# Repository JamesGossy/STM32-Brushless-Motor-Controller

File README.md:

<div align="center">

# STM32 Brushless Motor Controller

A custom four-layer motor controller with bare-metal field-oriented control on an STM32G474. The project includes the PCB design, C firmware, a motor simulator and a live control dashboard.

*Real motor bench test with the live telemetry dashboard.*

</div>

## Engineering overview

- **Hardware:** a 57 × 75 mm PCB with six MOSFETs, three low-side current shunts, absolute encoder feedback and CAN connectivity.
- **Control:** 20 kHz d/q current loops and SVPWM, a 2 kHz speed loop, decoupling feedforward and field weakening.
- **Firmware:** bare-metal C using CMSIS headers, with register-level peripheral drivers and no STM32 HAL dependency. The application code also runs in the software-in-the-loop simulator.
- **Calibration and protection:** current-sense polarity and encoder calibration, stored settings, and checks for current, voltage, temperature, encoder and communication faults.
- **Tools:** a browser dashboard for commands and telemetry, plus unit tests and simulated motor/fault scenarios.

```mermaid
flowchart LR
    control["STM32G474<br/>Field-oriented control"]
    power["DRV8353S & MOSFETs<br/>Three-phase bridge"]
    motor["BLDC / PMSM motor"]
    control -->|PWM| power --> motor
    motor -->|Current & rotor position| control

    classDef controller fill:#eef2ff,stroke:#6366f1,color:#1e1b4b
    classDef drive fill:#ecfdf5,stroke:#059669,color:#064e3b
    class control controller
    class power,motor drive
```

## Hardware

| Item | Design |
| --- | --- |
| MCU | STM32G474RET6, 170 MHz |
| Gate driver | TI DRV8353S, configured over SPI |
| Input range | 12–60 V design target |
| Phase current | 25 A continuous design target; firmware defaults to a 20 A limit |
| MOSFETs | Six IAUCN08S7N019ATMA1, 80 V |
| Current sensing | Three 2 mΩ shunts with Kelvin connections |
| Position feedback | MA730 SPI encoder; external quadrature interface |
| PWM | HRTIM, 20 kHz, 200 ns dead time |
| Interfaces | CAN, USB CDC, UART and SWD |
| PCB | 57 × 75 mm, four layers |

The layout keeps gate-drive loops short, separates current-sense connections from power routing, and uses copper pours and via arrays to distribute current and heat. KiCad sources and manufacturing files are in [`controller_hardware/`](controller_hardware/).

## Live dashboard

The dashboard connects to either the simulator or a board over USB. It shows motor telemetry and accepts commands for speed, torque, calibration and fault handling. The GIF above shows the simulator.

## Try the simulator

On Windows, run `controller_firmware\tools\setup.bat` to install missing tools, build the simulator and run tests. Then run `controller_firmware\tools\dashboard.bat` to open the dashboard.

For a manual build, install CMake, Ninja, a host C compiler and Python:

```sh
cd controller_firmware
cmake --preset sim
cmake --build --preset sim
ctest --preset sim
python -m pip install -r tools/dashboard/requirements.txt
python tools/dashboard/plot_motor.py --sim
```

Open [localhost:8988](http://localhost:8988). In the dashboard console, run `calibrate`, then `motor 3000` to request 3,000 rpm. Use `motor off` to stop. Simulator commands such as `sim load 0.1` and `sim lock on` exercise load response and fault handling.

## Build for the board

Install STM32CubeCLT and put its Arm compiler, CMake, Ninja and STM32 programmer on PATH. From `controller_firmware/`:

```sh
cmake --preset default
cmake --build --preset default
cmake --build build --target flash
```

Flashing uses ST-Link over SWD. To connect the dashboard to the board:

```sh
python tools/dashboard/plot_motor.py --serial COM5
```

Set the motor parameters and limits in [`app/config.h`](controller_firmware/app/config.h) before running hardware. Start with a current-limited supply and an unloaded motor, then run calibration before requesting motion.

## Validation and limits

C tests cover control maths, SVPWM, configuration, commands and telemetry. Software-in-the-loop tests exercise calibration, torque and speed response, field weakening, CAN control and fault handling. CI builds the firmware and runs simulator and dashboard tests on Linux and Windows.

The electrical ratings above are design targets; simulation does not establish continuous-current capability or thermal performance. This board revision has no on-board reverse-polarity protection, fuse or bus TVS.

## Code guide

| Location | Contents |
| --- | --- |
| [`controller_hardware/`](controller_hardware/) | KiCad schematics, PCB layout and manufacturing files |
| [`controller_firmware/app/`](controller_firmware/app/) | FOC, control loops, calibration, commands and telemetry |
| [`controller_firmware/hal/stm32g474/`](controller_firmware/hal/stm32g474/) | HRTIM, ADC, encoder, gate-driver, CAN and USB drivers |
| [`controller_firmware/sim/`](controller_firmware/sim/) | Simulated hardware interface, motor model and TCP server |
| [`controller_firmware/tests/`](controller_firmware/tests/) | Unit and motor simulation tests |
| [`controller_firmware/tools/dashboard/`](controller_firmware/tools/dashboard/) | Browser dashboard and Python bridge |

MIT licensed. Copyright © 2026 James Goss.

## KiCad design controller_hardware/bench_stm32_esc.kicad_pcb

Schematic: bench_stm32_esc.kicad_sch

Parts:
C1, C2, C3, C4, C7: EEHZC1K470V; CAP-SMD_BD10.0-L10.3-W10.3-FD; MPN EEHZC1K470V; LCSC Part C454280
C5, C12, C30, C31, C33, C41, C46, C47, C48, C49, C50, C53, C64, C65, C76, C83: 100nF; C_0402; Voltage Rated 16V; Tolerance ±10%; Part CL05B104KO5NNNC; LCSC C1525
C6, C38: 47nF; C_0603; Voltage Rated 100V; Tolerance ±10%; Part 0603B473K101CT; LCSC C559308
C8, C11, C20, C22: 100nF; C_0402; Voltage Rated 100V; Tolerance ±10%; Part GRM155R62A104KE14D; LCSC C162178
C9: GRM32EC72A106KE05L; C1210; MPN GRM32EC72A106KE05L; LCSC Part C576517
C10, C17, C19: 47uF; C_1206; Voltage Rated 16V; Tolerance ±20%; Part 1206X476M160NT; LCSC C172351
C13, C14, C15, C29, C36, C37, C42, C43, C45, C52, C93: 1uF; C_0402; Voltage Rated 25V; Tolerance ±10%; Part CL05A105KA5NQNC; LCSC C52923
C18, C26, C32: 2.2nF; C_0402; Voltage Rated 100V; Tolerance ±10%; Part CC0402KRX7R0BB222; LCSC C576731
C21, C24, C25: 1nF; C_0402; Voltage Rated 100V; Tolerance ±10%; Part CC0402KRX7R0BB102; LCSC C527013
C23, C27, C28: 1uF; C_1206; Voltage Rated 100V; Tolerance ±10%; Part CL31B105KCHNNNE; LCSC C13832
C39, C40: 2.2nF; C_0402; Voltage Rated 50V; Tolerance ±10%; Part 0402B222K500NT; LCSC C1531
C44: 4.7uF; C_0402; Voltage Rated 10V; Tolerance ±20%; Part CL05A475MP5NRNC; LCSC C23733
C51, C66, C67: 1nF; C_0402; Voltage Rated 50V; Tolerance ±10%; Part 0402B102K500NT; LCSC C1523
C54, C55: 2.2uF; C_0402; Voltage Rated 25V; Tolerance ±20%; Part GRM155R61E225ME15D; LCSC C72203
C56, C57, C58: 10nF; C_0402; Voltage Rated 50V; Tolerance ±10%; Part CL05B103KB5NNNC; LCSC C15195
C61, C62, C63: 47nF; C_0402; Voltage Rated 50V; Tolerance ±10%; Part 0402B473K500NT; LCSC C82219
C68, C69, C70, C71, C72, C73: 4.7uF; C_1206; Voltage Rated 100V; Tolerance ±10%; Part GRM31CC72A475KE11L; LCSC C237304
C85, C87: 18pF; C_0402; Voltage Rated 50V; Tolerance ±5%; Part 0402CG180J500NT; LCSC C1549
CN1, CN2, CN3: 1053141104; CONN-TH_4P-P2.50_MOLEX_1053141104; MPN 1053141104; LCSC Part C841207
D1: White; D_0603; Part KT-0603W; LCSC C2290
D2: Green; D_0805; Part KT-0805G; LCSC C2297
D3: PESD2CAN,215; SOT-23-3_L2.9-W1.3-P1.90-LS2.4-BR; MPN PESD2CAN,215; LCSC Part C75176
D4: Red; D_0805; Forward Voltage (VF) 1.6V~2.6V; Part NCD0805R1; LCSC C84256
D6: Yellow; D_0805; Part KT-0805Y; LCSC C2296
FB1: FB_0603; Current Rating 200mA; Tolerance ±25%; Part GZ1608D601TF; LCSC C1002
FB2: FB_0603; Current Rating 2A; Tolerance ±25%; Part BLM18PG121SN1D; LCSC C14709
H1, H2, H3, H4: MountingHole; MountingHole_3.2mm_M3
J1: Conn_02x01; PinHeader_2x01_P2.54mm_Vertical
J2: USB_C_Receptacle_USB2.0_16P; USB_C_Receptacle_HRO_TYPE-C-31-M-12
J3: Conn_ARM_SWD_TagConnect_TC2030-NL; Tag-Connect_TC2030-IDC-NL_2x03_P1.27mm_Vertical
J4: Screw_Terminal_01x05; CUI_TB005_-762-05BE
L1: FNR4020S8R2MT; IND-SMD_L4.0-W4.0_FNR40XXS; MPN FNR4020S8R2MT; LCSC Part C167834
NT1, NT2, NT3, NT4, NT5, NT6: NetTie_2; NetTie-2_SMD_Pad0.5mm
NT7: NetTie_2; NetTie-2_SMD_Pad2.0mm
Q1, Q2, Q3, Q4, Q5, Q6: IAUCN08S7N019ATMA1; TDSON-8-1; LCSC C33993693
R1, R2, R42, R44, R45, R46, R47, R48, R49, R56: 100Ω; R_0402; Overload Voltage (Max) 50V; Tolerance ±1%; Part 0402WGF1000TCE; LCSC C25076
R3, R4, R5: 330Ω; R_0402; Overload Voltage (Max) 50V; Tolerance ±1%; Part 0402WGF3300TCE; LCSC C25104
R6, R23, R51: 100kΩ; R_0402; Overload Voltage (Max) 50V; Tolerance ±1%; Part 0402WGF1003TCE; LCSC C25741
R7, R10, R13: 2.7Ω; R_0805; Overload Voltage (Max) 150V; Tolerance ±1%; Part 0805W8F270KT5E; LCSC C17532
R8, R9, R12: 2mΩ; R_2512_6332Metric; Part No HoLLR2512-3W-2mR-1%; LCSC C2994640
R11: 19.1kΩ; R_0402; Overload Voltage (Max) 50V; Part 0402WGF1912TCE; LCSC C52036
R14: 120Ω; R_0402; Overload Voltage (Max) 50V; Tolerance ±1%; Part 0402WGF1200TCE; LCSC C25079
R15, R16, R20: 56Ω; R_0402; Overload Voltage (Max) 50V; Tolerance ±1%; Part 0402WGF560JTCE; LCSC C25127
R17, R21: 4.7kΩ; R_0402; Overload Voltage (Max) 50V; Tolerance ±1%; Part 0402WGF4701TCE; LCSC C25900
R18: 383kΩ; R_0805; Overload Voltage (Max) 150V; Tolerance ±1%; Part 0805W8F3833T5E; LCSC C17652
R19: 9.76kΩ; R_0805; Overload Voltage (Max) 150V; Tolerance ±1%; Part 0805W8F9761T5E; LCSC C17859
R22, R24, R43, R50, R53: 10kΩ; R_0402; Overload Voltage (Max) 50V; Tolerance ±1%; Part 0402WGF1002TCE; LCSC C25744
R25, R26, R27, R28, R31, R32: 10Ω; R_0402; Overload Voltage (Max) 50V; Tolerance ±1%; Part 0402WGF100JTCE; LCSC C25077
R29, R30: 5.1kΩ; R_0402; Overload Voltage (Max) 50V; Tolerance ±1%; Part 0402WGF5101TCE; LCSC C25905
R33, R35, R37: 383kΩ; R_0402; Overload Voltage (Max) 75V; Tolerance ±1%; Part RK73H1ETTP3833F; LCSC C317011
R34, R36, R41, R55: 1kΩ; R_0402; Overload Voltage (Max) 50V; Tolerance ±1%; Part 0402WGF1001TCE; LCSC C11702
R38, R39, R40: 9.76kΩ; R_0402; Overload Voltage (Max) 50V; Tolerance ±1%; Part FRC0402F9761TS; LCSC C2998101
R52, R54: 20kΩ; R_0402; Overload Voltage (Max) 50V; Tolerance ±1%; Part 0402WGF2002TCE; LCSC C25765
S1, S2: Tactile Button, 160gf; SW_TS-1088-AR02016; Voltage Rating (Dc) 12V; Part TS-1088-AR02016; LCSC C720477
TH1, TH2: Thermistor_NTC; R_0603; Part No KNTC0603/10KF3950; LCSC C2892547
TP1, TP6, TP7, TP8, TP9, TP10, TP11, TP12, TP13: TestPoint; TestPoint_Pad_1.5x1.5mm
U1: LMR51635YDDCR; SOT-23-6_L2.9-W1.6-P0.95-LS2.8-BL; MPN LMR51635YDDCR; LCSC Part C45262770
U2: MA730; QFN-16-1EP_3x3mm_P0.5mm_EP1.75x1.75mm
U3: TPD1E05U06DYA; D_SOD-523
U4: DRV8353SRTAR; WQFN-40_L6.0-W6.0-P0.50-TL-EP4.5; MPN DRV8353SRTAR; LCSC Part C701785
U5: LM66200DRLR; SOT-583-8_L2.1-W1.2-P0.50-LS1.6-BL; MPN LM66200DRLR; LCSC Part C3235556
U6: AP2112K-3.3; SOT-23-5
U7: STM32G474RETx; LQFP-64_10x10mm_P0.5mm
U8: TCAN1462VDRBRQ1; DFN-8_L3.0-W3.0-P0.65-TL-EP2.4; MPN TCAN1462VDRBRQ1; LCSC Part C5215833
U20: USBLC6-2P6; SOT-666
X1: X322524MOB4SI; CRYSTAL-SMD_4P-L3.2-W2.5-BL; MPN X322524MOB4SI; LCSC Part C70590

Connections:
5V_OR: C31.2, C36.1, C43.1, CN3.2, TP12.1 (1_1), U5.2 (VOUT), U5.7 (VOUT), U6.1 (VIN), U6.3 (EN), U8.3 (VCC)
+3V3: C11.1, C29.1, C30.1, C33.2, C44.1, C45.1, C46.1, C47.1, C48.1, C49.1, C53.1, C93.1, D4.2, D6.2, FB1.2, J3.1 (VCC), R17.1, R21.1, R22.1, R23.1, R43.1, R55.1, S2.1 (A), TP13.1 (1_1), U2.13 (VDD), U4.24 (VREF), U6.5 (VOUT), U7.1 (VBAT), U7.16 (VDD), U7.32 (VDD), U7.48 (VDD), U7.64 (VDD), U8.5 (NC/VIO)
+3V3A: C50.1, C52.1, C83.1, FB1.1, U7.28 (VREF+), U7.29 (VDDA)
+5V_BUCK: C10.1, C17.1, C19.1, C37.1, L1.2, R6.1, U5.6 (VIN2)
+5V_USB: C42.1, C55.1, FB2.2, U5.3 (VIN1)
/AMB_TMP: C12.1, R21.2, R48.1, TH2.1
/AMB_TMP_ADC: C64.1, R48.2, U7.10 (PC2)
/BOOT0: R24.1, S2.2 (B), U7.61 (PB8)
/CANH: CN1.4, CN2.4, D3.1, J1.2, U8.7 (CANH)
/CANL: CN1.3, CN2.3, D3.2, R14.1, U8.6 (CANL)
/CAN_RX: U7.58 (PB5), U8.4 (RXD)
/CAN_TX: U7.59 (PB6), U8.1 (TXD)
/CB: C22.2, U1.6 (CB)
/CC1: J2.A5 (CC1), R30.1
/CC2: J2.B5 (CC2), R29.1
/CPH: C6.2, U4.2 (CPH)
/CPL: C6.1, U4.1 (CPL)
/D+: J2.A6 (D+), J2.B6 (D+), U20.1 (I/O2)
/D-: J2.A7 (D-), J2.B7 (D-), U20.6 (I/O1)
/DVDD: C15.1, U4.38 (DVDD)
/ENABLE: D2.2, U4.31 (ENABLE), U7.57 (PB4)
/ENC_CS: U2.5 (~CS), U7.33 (PB11)
/FAULT: R4.2, R22.2, U4.26 (nFAULT)
/FB: R6.2, R11.1, U1.1 (FB)
/GD_CS: R43.2, U4.30 (nSCS), U7.52 (PC10)
/GHA: R27.1, U4.6 (GHA)
/GHA_R: Q1.4 (G), R27.2
/GHB: R26.1, U4.15 (GHB)
/GHB_R: Q3.4 (G), R26.2
/GHC: R25.1, U4.16 (GHC)
/GHC_R: Q5.4 (G), R25.2
/GLA: R32.1, U4.8 (GLA)
/GLA_R: Q2.4 (G), R32.2
/GLB: R31.1, U4.13 (GLB)
/GLB_R: Q4.4 (G), R31.2
/GLC: R28.1, U4.18 (GLC)
/GLC_R: Q6.4 (G), R28.2
/HEARBEAT: D1.2, U7.18 (PA4)
/HSE_IN: C87.1, U7.5 (PF0), X1.3 (OSC2)
/HSE_OUT: C85.1, U7.6 (PF1), X1.1 (OSC1)
/IA: C56.1, R20.1, U7.37 (PB15)
/IB: C57.1, R16.1, U7.36 (PB14)
/IC: C58.1, R15.1, U7.35 (PB13)
/INHA: U4.32 (INHA), U7.43 (PA9)
/INHB: U4.34 (INHB), U7.41 (PC9)
/INHC: U4.36 (INHC), U7.39 (PC7)
/INLA: U4.33 (INLA), U7.42 (PA8)
/INLB: U4.35 (INLB), U7.40 (PC8)
/INLC: U4.37 (INLC), U7.38 (PC6)
/MOTA: C18.1, J4.2, NT1.2, Q1.1 (S), Q1.2 (S), Q1.3 (S), Q2.5 (D), R33.1, TP8.1 (1_1)
/MOTB: C26.1, J4.3, NT3.2, Q3.1 (S), Q3.2 (S), Q3.3 (S), Q4.5 (D), R35.1, TP6.1 (1_1)
/MOTC: C32.1, J4.5, NT5.2, Q5.1 (S), Q5.2 (S), Q5.3 (S), Q6.5 (D), R37.1, TP7.1 (1_1)
/NRST: C76.1, J3.3 (~RESET), S1.2 (B), U7.7 (PG10)
/ON: R51.1, U5.4 (~ON)
/PHASE_TMP: C5.1, R17.2, R49.1, TH1.1
/PHASE_TMP_ADC: C65.1, R49.2, U7.11 (PC3)
/QUAD_CH1: C40.1, R50.2, R52.1, U7.12 (PA0)
/QUAD_CH1_CONN: CN3.4, R50.1
/QUAD_CH2: C39.1, R53.2, R54.1, U7.13 (PA1)
/QUAD_CH2_CONN: CN3.3, R53.1
/SHA: NT1.1, U4.7 (SHA)
/SHB: NT3.1, U4.14 (SHB)
/SHC: NT5.1, U4.17 (SHC)
/SNA: NT2.1, R2.2
/SNA_FILT: C21.2, R2.1, U4.10 (SNA)
/SNB: NT4.1, R44.2
/SNB_FILT: C24.2, R44.1, U4.11 (SNB)
/SNC: NT6.1, R46.2
/SNC_FILT: C25.2, R46.1, U4.20 (SNC)
/SOA: R20.2, U4.23 (SOA)
/SOB: R16.2, U4.22 (SOB)
/SOC: R15.2, U4.21 (SOC)
/SPA: Q2.1 (S), Q2.2 (S), Q2.3 (S), R1.2, R8.1
/SPA_FILT: C21.1, R1.1, U4.9 (SPA)
/SPB: Q4.1 (S), Q4.2 (S), Q4.3 (S), R9.1, R42.2
/SPB_FILT: C24.1, R42.1, U4.12 (SPB)
/SPC: Q6.1 (S), Q6.2 (S), Q6.3 (S), R12.1, R45.2
/SPC_FILT: C25.1, R45.1, U4.19 (SPC)
/SPI_MISO: R55.2, U2.7 (MISO), U4.27 (SDO), U7.20 (PA6)
/SPI_MOSI: U2.4 (MOSI), U4.28 (SDI), U7.21 (PA7)
/SPI_SCK: U2.12 (SCLK), U4.29 (SCLK), U7.19 (PA5)
/ST: R23.2, U5.8 (ST)
/SW: C22.1, L1.1, U1.5 (SW)
/SWCLK: J3.4 (SWCLK), U7.50 (PA14)
/SWDIO: J3.2 (SWDIO), U7.49 (PA13)
/SWO: J3.6 (SWO), U7.56 (PB3)
/USB_D+: U7.46 (PA12), U20.3 (I/O2)
/USB_D-: U7.45 (PA11), U20.4 (I/O1)
/USB_VBUS: C54.1, FB2.1, J2.A4 (VBUS), J2.A9 (VBUS), J2.B4 (VBUS), J2.B9 (VBUS), U20.5 (VBUS)
/VA_ADC: C51.1, R41.1, U7.26 (PB2)
/VB_ADC: C66.1, R36.1, U7.25 (PB1)
/VCP: C14.1, U4.5 (VCP)
/VC_ADC: C67.1, R34.1, U7.24 (PB0)
/VDC_ADC: C41.1, R47.2, U7.9 (PC1)
/VDRAIN: C14.2, NT7.1, U4.4 (VDRAIN)
/VGLS: C13.1, U4.40 (VGLS)
/VSENA: C61.1, R33.2, R40.1, R41.2
/VSENB: C62.1, R35.2, R36.2, R39.1
/VSENC: C63.1, R34.2, R37.2, R38.1
/VSENVM: C38.1, R18.2, R19.1, R47.1, U3.1 (I/O)
GND: C1.2, C2.2, C3.2, C4.2, C5.2, C7.2, C8.2, C9.1, C10.2, C11.2, C12.2, C13.2, C15.2, C17.2, C19.2, C20.2, C23.1, C27.1, C28.1, C29.2, C30.2, C31.1, C33.1, C36.2, C37.2, C38.2, C39.2, C40.2, C41.2, C42.2, C43.2, C44.2, C45.2, C46.2, C47.2, C48.2, C49.2, C50.2, C51.2, C52.2, C53.2, C54.2, C55.2, C56.2, C57.2, C58.2, C61.2, C62.2, C63.2, C64.2, C65.2, C66.2, C67.2, C68.2, C69.2, C70.2, C71.2, C72.2, C73.2, C76.2, C83.2, C85.2, C87.2, C93.2, CN1.1, CN1.2, CN2.1, CN2.2, CN3.1, D3.3, J2.A1 (GND), J2.A12 (GND), J2.B1 (GND), J2.B12 (GND), J2.SH (SHIELD), J3.5 (GND), J4.4, NT2.2, NT4.2, NT6.2, R3.2, R5.2, R7.2, R8.2, R9.2, R10.2, R11.2, R12.2, R13.2, R19.2, R24.2, R29.2, R30.2, R38.2, R39.2, R40.2, R51.2, R52.2, R54.2, R56.2, S1.1 (A), TH1.2, TH2.2, TP9.1 (1_1), TP10.1 (1_1), TP11.1 (1_1), U1.4 (GND), U2.8 (GND), U2.10 (TEST), U2.17 (PAD), U3.2 (GND), U4.25 (AGND), U4.39 (GND), U4.41 (EP), U5.1 (GND), U5.5 (GND), U6.2 (GND), U7.15 (VSS), U7.27 (VSSA), U7.31 (VSS), U7.47 (VSS), U7.63 (VSS), U8.2 (GND), U8.8 (STB), U8.9 (EP), U20.2 (GND), X1.2 (GND), X1.4 (GND)
unnamed: C18.2, R7.1
unnamed: C26.2, R10.1
unnamed: C32.2, R13.1
unnamed: D1.1, R56.1
unnamed: D2.1, R3.1
unnamed: D4.1, R4.1
unnamed: D6.1, R5.1
unnamed: J1.1, R14.2
VM: C1.1, C2.1, C3.1, C4.1, C7.1, C8.1, C9.2, C20.1, C23.2, C27.2, C28.2, C68.1, C69.1, C70.1, C71.1, C72.1, C73.1, J4.1, NT7.2, Q1.5 (D), Q3.5 (D), Q5.5 (D), R18.1, TP1.1 (1_1), U1.2 (EN), U1.3 (VIN), U4.3 (VM)

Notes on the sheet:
Phase A
CAN Transciever + Connectors
VM to 5V Buck
Power ORing + LDO
Crystal
STM32G474
Quadrature Encoder Connector
LED Indicators
DRV8353
Input Voltage
Phase B
SPI MA730 Encoder
Temp Sensing
Phase C
Mounting Holes
USB-C Connector
SWD Connector

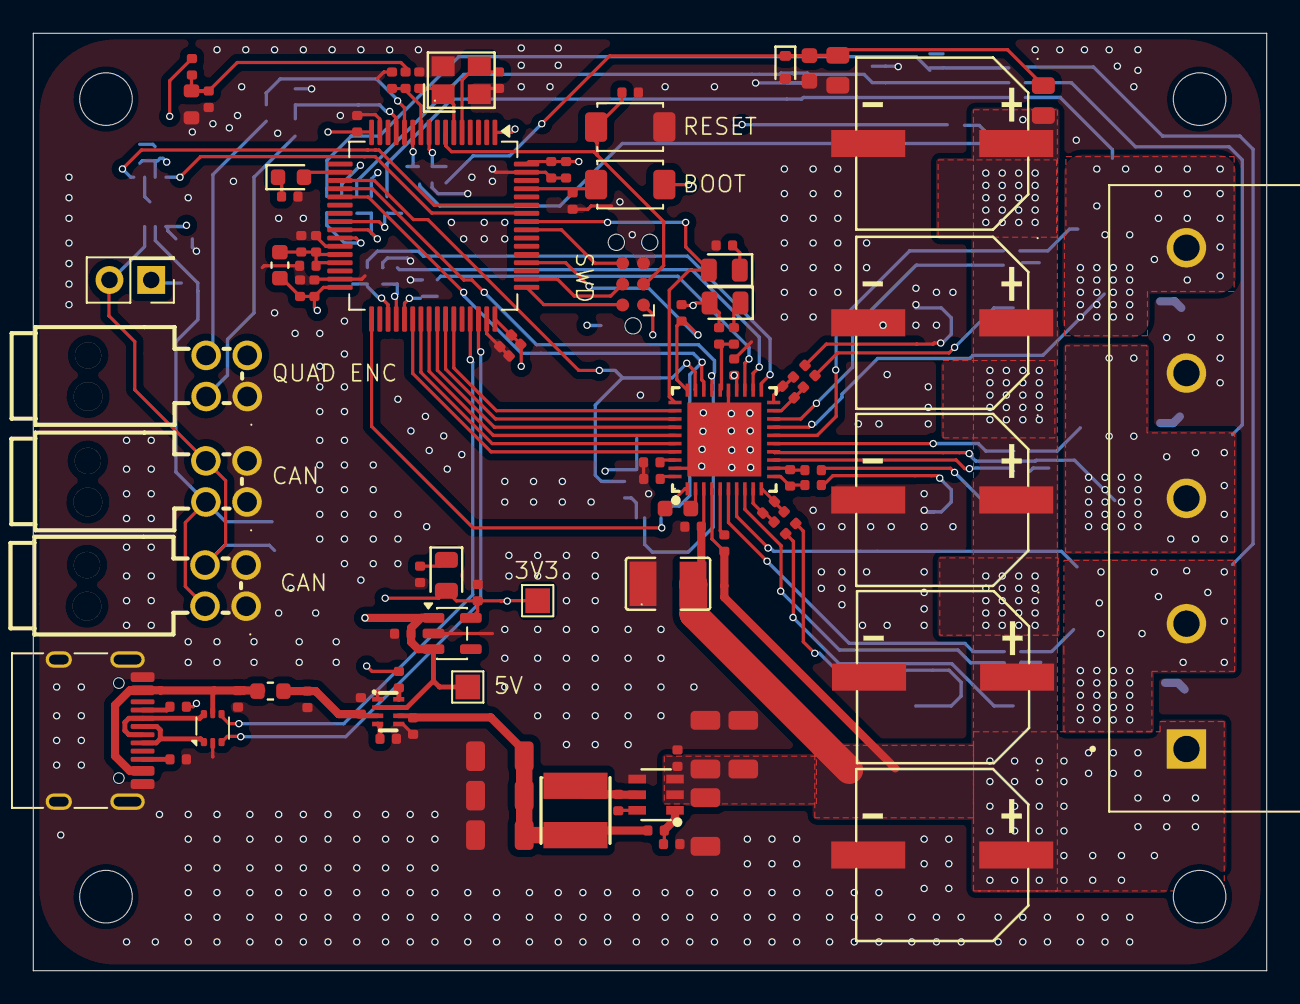
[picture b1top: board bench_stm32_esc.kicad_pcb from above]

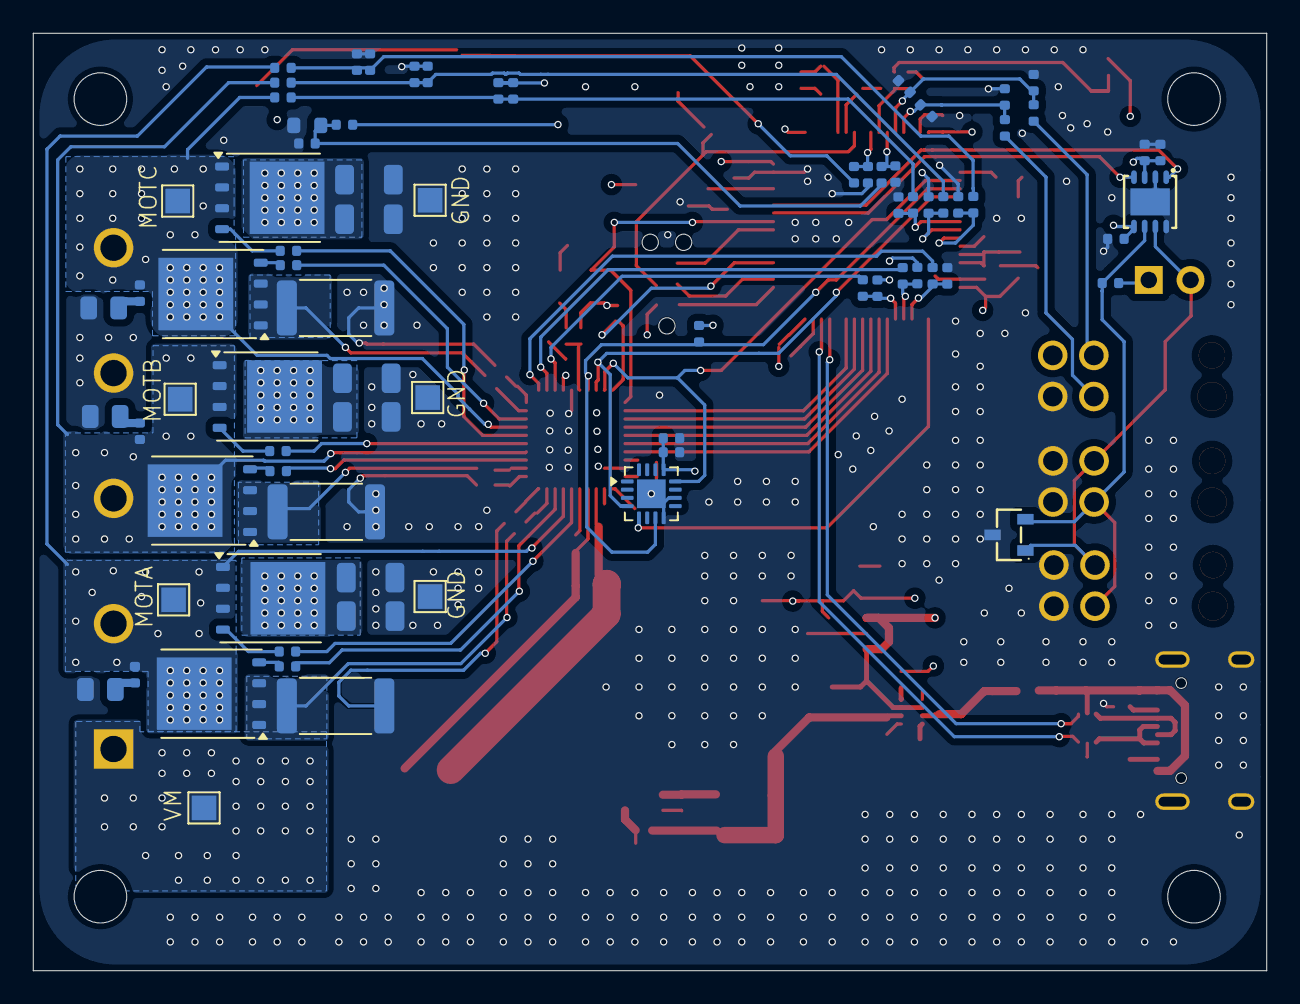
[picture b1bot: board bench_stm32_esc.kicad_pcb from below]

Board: 4 copper layers, 75.0 x 57.0 mm, 184 parts (81 on the bottom side), 110 nets.

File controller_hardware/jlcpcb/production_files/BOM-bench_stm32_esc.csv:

Comment,Designator,Footprint,LCSC,Quantity
100kΩ,"R23,R51,R6",R_0402,C25741,3
100nF,"C12,C30,C31,C33,C41,C46,C47,C48,C49,C5,C50,C53,C64,C65,C76,C83",C_0402,C1525,16
100nF,"C11,C20,C22,C8",C_0402,C162178,4
100Ω,"R1,R2,R42,R44,R45,R46,R47,R48,R49,R56",R_0402,C25076,10
1053141104,"CN1,CN2,CN3",CONN-TH_4P-P2.50_MOLEX_1053141104,C841207,3
10kΩ,"R22,R24,R43,R50,R53",R_0402,C25744,5
10nF,"C56,C57,C58",C_0402,C15195,3
10Ω,"R25,R26,R27,R28,R31,R32",R_0402,C25077,6
120Ω,R14,R_0402,C25079,1
18pF,"C85,C87",C_0402,C1549,2
19.1kΩ,R11,R_0402,C52036,1
1kΩ,"R34,R36,R41,R55",R_0402,C11702,4
1nF,"C51,C66,C67",C_0402,C1523,3
1nF,"C21,C24,C25",C_0402,C527013,3
1uF,"C23,C27,C28",C_1206,C13832,3
1uF,"C13,C14,C15,C29,C36,C37,C42,C43,C45,C52,C93",C_0402,C52923,11
2.2nF,"C39,C40",C_0402,C1531,2
2.2nF,"C18,C26,C32",C_0402,C576731,3
2.2uF,"C54,C55",C_0402,C72203,2
2.7Ω,"R10,R13,R7",R_0805,C17532,3
20kΩ,"R52,R54",R_0402,C25765,2
2mΩ,"R12,R8,R9",R_2512_6332Metric,C2994640,3
330Ω,"R3,R4,R5",R_0402,C25104,3
383kΩ,R18,R_0805,C17652,1
383kΩ,"R33,R35,R37",R_0402,C317011,3
4.7kΩ,"R17,R21",R_0402,C25900,2
4.7uF,"C68,C69,C70,C71,C72,C73",C_1206,C237304,6
4.7uF,C44,C_0402,C23733,1
47nF,"C38,C6",C_0603,C559308,2
47nF,"C61,C62,C63",C_0402,C82219,3
47uF,"C10,C17,C19",C_1206,C172351,3
5.1kΩ,"R29,R30",R_0402,C25905,2
56Ω,"R15,R16,R20",R_0402,C25127,3
9.76kΩ,R19,R_0805,C17859,1
9.76kΩ,"R38,R39,R40",R_0402,C2998101,3
DRV8353SRTAR,U4,WQFN-40_L6.0-W6.0-P0.50-TL-EP4.5,C701785,1
EEHZC1K470V,"C1,C2,C3,C4,C7",CAP-SMD_BD10.0-L10.3-W10.3-FD,C454280,5
FNR4020S8R2MT,L1,IND-SMD_L4.0-W4.0_FNR40XXS,C167834,1
GRM32EC72A106KE05L,C9,C1210,C576517,1
Green,D2,D_0805,C2297,1
IAUCN08S7N019ATMA1,"Q1,Q2,Q3,Q4,Q5,Q6",TDSON-8-1,C33993693,6
LM66200DRLR,U5,SOT-583-8_L2.1-W1.2-P0.50-LS1.6-BL,C3235556,1
LMR51635YDDCR,U1,SOT-23-6_L2.9-W1.6-P0.95-LS2.8-BL,C45262770,1
"PESD2CAN,215",D3,SOT-23-3_L2.9-W1.3-P1.90-LS2.4-BR,C75176,1
Red,D4,D_0805,C84256,1
TCAN1462VDRBRQ1,U8,DFN-8_L3.0-W3.0-P0.65-TL-EP2.4,C5215833,1
"Tactile Button, 160gf","S1,S2",SW_TS-1088-AR02016,C720477,2
Thermistor_NTC,"TH1,TH2",R_0603,C2892547,2
White,D1,D_0603,C2290,1
X322524MOB4SI,X1,CRYSTAL-SMD_4P-L3.2-W2.5-BL,C70590,1
Yellow,D6,D_0805,C2296,1
~,FB1,FB_0603,C1002,1
~,FB2,FB_0603,C14709,1
TestPoint,TP13,TestPoint_Pad_1.5x1.5mm,,1
TestPoint,TP12,TestPoint_Pad_1.5x1.5mm,,1
AP2112K-3.3,U6,SOT-23-5,,1
USBLC6-2P6,U20,SOT-666,,1
STM32G474RETx,U7,LQFP-64_10x10mm_P0.5mm,,1
MA730,U2,QFN-16-1EP_3x3mm_P0.5mm_EP1.75x1.75mm,,1
USB_C_Receptacle_USB2.0_16P,J2,USB_C_Receptacle_HRO_TYPE-C-31-M-12,,1
Screw_Terminal_01x05,J4,CUI_TB005_-762-05BE,,1
Conn_02x01,J1,PinHeader_2x01_P2.54mm_Vertical,,1
TPD1E05U06DYA,U3,D_SOD-523,,1
TestPoint,TP9,TestPoint_Pad_1.5x1.5mm,,1
TestPoint,TP8,TestPoint_Pad_1.5x1.5mm,,1
TestPoint,TP1,TestPoint_Pad_1.5x1.5mm,,1
TestPoint,TP11,TestPoint_Pad_1.5x1.5mm,,1
TestPoint,TP10,TestPoint_Pad_1.5x1.5mm,,1
TestPoint,TP7,TestPoint_Pad_1.5x1.5mm,,1
TestPoint,TP6,TestPoint_Pad_1.5x1.5mm,,1

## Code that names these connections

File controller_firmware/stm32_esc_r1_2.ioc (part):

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Mcu.Name=STM32G474R(B-C-E)Tx
Mcu.Package=LQFP64
Mcu.UserName=STM32G474RETx
PA0.GPIOParameters=GPIO_Label
PA0.GPIO_Label=QUAD_CH1
PA0.Signal=S_TIM2_CH1
PA1.GPIOParameters=GPIO_Label
PA1.GPIO_Label=QUAD_CH2
PA1.Signal=S_TIM2_CH2
PA11.Mode=Device
PA11.Signal=USB_DM
PA12.Mode=Device
PA12.Signal=USB_DP
PA13.Mode=Trace_Asynchronous_SW
PA13.Signal=SYS_JTMS-SWDIO
PA14.Mode=Trace_Asynchronous_SW
PA14.Signal=SYS_JTCK-SWCLK
PA4.GPIOParameters=GPIO_Label
PA4.GPIO_Label=HEARTBEAT
PA4.Signal=GPIO_Output
PA5.Mode=Full_Duplex_Master
PA5.Signal=SPI1_SCK
PA6.Mode=Full_Duplex_Master
PA6.Signal=SPI1_MISO
PA7.Mode=Full_Duplex_Master
PA7.Signal=SPI1_MOSI
PA8.GPIOParameters=GPIO_Label
PA8.GPIO_Label=INLA
PA8.Mode=Output_TA1TA2
PA8.Signal=HRTIM1_CHA1
PA9.GPIOParameters=GPIO_Label
PA9.GPIO_Label=INHA
PA9.Mode=Output_TA1TA2
PA9.Signal=HRTIM1_CHA2
PB0.GPIOParameters=GPIO_Label
PB0.GPIO_Label=VC_ADC
PB0.Mode=IN15-Single-Ended
PB0.Signal=ADC1_IN15
PB1.GPIOParameters=GPIO_Label
PB1.GPIO_Label=VB_ADC
PB1.Mode=IN1-Single-Ended
PB1.Signal=ADC3_IN1
PB11.GPIOParameters=GPIO_Label
PB11.GPIO_Label=ENC_CS
PB11.Signal=GPIO_Output
PB13.GPIOParameters=GPIO_Label
PB13.GPIO_Label=IC
PB13.Mode=IN5-Single-Ended
PB13.Signal=ADC3_IN5
PB14.GPIOParameters=GPIO_Label
PB14.GPIO_Label=IB
PB14.Mode=IN5-Single-Ended
PB14.Signal=ADC1_IN5
PB15.GPIOParameters=GPIO_Label
PB15.GPIO_Label=IA
PB15.Mode=IN15-Single-Ended
PB15.Signal=ADC2_IN15
PB2.GPIOParameters=GPIO_Label
PB2.GPIO_Label=VA_ADC
PB2.Mode=IN12-Single-Ended
PB2.Signal=ADC2_IN12
PB3.Mode=Trace_Asynchronous_SW
PB3.Signal=SYS_JTDO-SWO
PB4.GPIOParameters=GPIO_Label
PB4.GPIO_Label=ENABLE
PB4.Signal=GPIO_Output
PB5.Mode=FDCAN_Activate
PB5.Signal=FDCAN2_RX
PB6.Mode=FDCAN_Activate
PB6.Signal=FDCAN2_TX
PC1.GPIOParameters=GPIO_Label
PC1.GPIO_Label=VDC_ADC
PC1.Mode=IN7-Single-Ended
PC1.Signal=ADC1_IN7
PC10.GPIOParameters=GPIO_Label
PC10.GPIO_Label=GD_CS
PC10.Signal=GPIO_Output
PC2.GPIOParameters=GPIO_Label
PC2.GPIO_Label=AMB_TMP_ADC
PC2.Mode=IN8-Differential
PC2.Signal=ADC1_IN8
PC3.GPIOParameters=GPIO_Label
PC3.GPIO_Label=PHASE_TMP_ADC
PC3.Mode=IN8-Differential
PC3.Signal=ADC1_IN9
PC6.GPIOParameters=GPIO_Label
PC6.GPIO_Label=INLC
PC6.Mode=Output_TF1TF2
PC6.Signal=HRTIM1_CHF1
PC7.GPIOParameters=GPIO_Label
PC7.GPIO_Label=INHC
PC7.Mode=Output_TF1TF2
PC7.Signal=HRTIM1_CHF2
PC8.GPIOParameters=GPIO_Label
PC8.GPIO_Label=INLB
PC8.Mode=Output_TE1TE2
PC8.Signal=HRTIM1_CHE1
PC9.GPIOParameters=GPIO_Label
PC9.GPIO_Label=INHB
PC9.Mode=Output_TE1TE2
PC9.Signal=HRTIM1_CHE2
PF0-OSC_IN.Mode=HSE-External-Oscillator
PF0-OSC_IN.Signal=RCC_OSC_IN
PF1-OSC_OUT.Mode=HSE-External-Oscillator
PF1-OSC_OUT.Signal=RCC_OSC_OUT
RCC.HSE_VALUE=8000000
RCC.SYSCLKFreq_VALUE=144000000
RCC.SYSCLKSource=RCC_SYSCLKSOURCE_PLLCLK
board=custom

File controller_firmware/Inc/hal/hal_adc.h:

#pragma once

#include <stdint.h>

/*
 * hal_adc.h — ADC for current sense and DC bus voltage
 *
 * Pin / ADC mapping (from peripheral_setup.txt):
 *   PA1 / ADC2_IN2  -> SOA  (phase A shunt amp output)
 *   PA0 / ADC1_IN1  -> SOB  (phase B shunt amp output)  [ADC1 not yet wired; use ADC2_IN1 if rerouted]
 *   PB1 / ADC3_IN1  -> VSENVM  (DC bus voltage divider)
 *   PB11/ ADC2_IN14 -> AMBIENT_TMP
 *   PB12/ ADC4_IN3  -> PHASE_TMP
 *
 * All conversions are software-triggered (polling), injected into the background loop.
 *
 * DC bus voltage conversion factor:
 *   Board uses a resistor divider — adjust ADC_VBUS_SCALE to match your divider ratio.
 *   Default assumes 100k / 4.7k -> Vbus = Vadc * (100 + 4.7) / 4.7 ≈ Vadc * 22.28
 *   (Tune this to your actual resistor values.)
 */

#define ADC_VREF_V          3.3f
#define ADC_FULL_SCALE      4095.0f

/* NTC thermistor scaling: 10kΩ B=3950 on bottom of divider, 4.7kΩ pull-up to 3.3V
 * R_NTC = 4700 * Vadc / (3.3 - Vadc)
 * T(°C) = 1 / (ln(R_NTC / 10000) / 3950 + 1/298.15) - 273.15 */
#define ADC_NTC_RPULLUP     4700.0f
#define ADC_NTC_R25         10000.0f
#define ADC_NTC_B           3950.0f
#define ADC_NTC_T25         298.15f   /* 25°C in Kelvin */
#define ADC_VBUS_SCALE      40.25f   /* 383k / 9.76k divider: (383 + 9.76) / 9.76 */

/* Current sense scaling: DRV8353 CSA gain=10 V/V, 7 mΩ shunt, VREF=3.3V
 * SOx = VREF/2 + (I * Rshunt * gain)  =>  I = (SOx - VREF/2) / (Rshunt * gain) */
#define ADC_CSA_VBIAS       (ADC_VREF_V / 2.0f)   /* 1.65 V output at zero current */
#define ADC_CSA_GAIN        10.0f
#define ADC_CSA_RSHUNT      0.007f                 /* 7 mΩ */
#define ADC_CSA_SCALE       (1.0f / (ADC_CSA_RSHUNT * ADC_CSA_GAIN))  /* V -> A */

void  ADC_Init(void);
void  ADC_ConvertCurrents(void);                 /* call from TIM1 ISR — converts DMA result to Amperes */
void  ADC_Sample(void);                          /* call from main loop — updates Vbus and temperatures */
void  ADC_Sample_Raw(float *vsoA, float *vsoB);  /* accumulates raw SOx volts, used during CSA calibration */
void  ADC_RearmHwTrigger(void);                  /* call once after CSA calibration loop */

extern volatile float g_adcSoA;          /* phase A current (A), offset-corrected */
extern volatile float g_adcSoB;          /* phase B current (A), offset-corrected */
extern volatile float g_adcSoA_offset;   /* amp offset in volts, set by DRV835x_CalibrateCSA */
extern volatile float g_adcSoB_offset;
extern volatile float g_adcVbus;      /* DC bus voltage (V) */
extern volatile float g_adcAmbTemp;   /* ambient temp sense (V) */
extern volatile float g_adcPhaseTemp; /* phase temp sense (V) */

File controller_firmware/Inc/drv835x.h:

#pragma once

#include <stdint.h>

/*
 * drv835x.h — DRV8350S / DRV8353S SPI register interface
 *
 * SPI frame (16-bit, MSB first):
 *   Bit 15:    R/W (1=read, 0=write)
 *   Bits 14-11: register address (4 bits)
 *   Bits 10-0:  data (11 bits)
 *
 * Register map (SPI variant, section 8.6 of SLVSDY6):
 *   0x00  Fault Status 1  (read-only)
 *   0x01  VGS Status 2    (read-only)
 *   0x02  Driver Control
 *   0x03  Gate Drive HS
 *   0x04  Gate Drive LS
 *   0x05  OCP Control
 *   0x06  CSA Control
 */

/* Register addresses */
#define DRV835X_REG_FAULT_STATUS1   0x00u
#define DRV835X_REG_VGS_STATUS2     0x01u
#define DRV835X_REG_DRIVER_CTRL     0x02u
#define DRV835X_REG_GATE_DRIVE_HS   0x03u
#define DRV835X_REG_GATE_DRIVE_LS   0x04u
#define DRV835X_REG_OCP_CTRL        0x05u
#define DRV835X_REG_CSA_CTRL        0x06u

/* CSA Control register bits */
#define DRV835X_CSA_GAIN_5          (0u << 6)   /* 5 V/V  */
#define DRV835X_CSA_GAIN_10         (1u << 6)   /* 10 V/V */
#define DRV835X_CSA_GAIN_20         (2u << 6)   /* 20 V/V (power-on default) */
#define DRV835X_CSA_GAIN_40         (3u << 6)   /* 40 V/V */
#define DRV835X_CSA_VREF_DIV        (1u << 9)   /* SOx bias = VREF/2 (default) */
#define DRV835X_CSA_CAL_A           (1u << 4)   /* short SPA/SNA -> measures amp offset */
#define DRV835X_CSA_CAL_B           (1u << 3)   /* short SPB/SNB */
#define DRV835X_CSA_CAL_C           (1u << 2)   /* short SPC/SNC */

/* Fault Status 1 bit masks */
#define DRV835X_FAULT       (1u << 10)   /* any fault latched */
#define DRV835X_VDS_OCP     (1u <<  9)   /* VDS overcurrent (any FET) */
#define DRV835X_GDF         (1u <<  8)   /* gate drive fault */
#define DRV835X_UVLO        (1u <<  7)   /* undervoltage lockout */
#define DRV835X_OTSD        (1u <<  6)   /* overtemp shutdown */
#define DRV835X_VDS_HA      (1u <<  5)   /* VDS OCP high-side A */
#define DRV835X_VDS_LA      (1u <<  4)   /* VDS OCP low-side A */
#define DRV835X_VDS_HB      (1u <<  3)   /* VDS OCP high-side B */
#define DRV835X_VDS_LB      (1u <<  2)   /* VDS OCP low-side B */
#define DRV835X_VDS_HC      (1u <<  1)   /* VDS OCP high-side C */
#define DRV835X_VDS_LC      (1u <<  0)   /* VDS OCP low-side C */

/* VGS Status 2 bit masks */
#define DRV835X_SA_OC       (1u <<  10)  /* sense amp A overcurrent */
#define DRV835X_SB_OC       (1u <<  9)   /* sense amp B overcurrent */
#define DRV835X_SC_OC       (1u <<  8)   /* sense amp C overcurrent */
#define DRV835X_OTW         (1u <<  7)   /* overtemp warning */
#define DRV835X_GDUV        (1u <<  6)   /* gate drive undervoltage */
#define DRV835X_VGS_HA      (1u <<  5)   /* VGS fault high-side A */
#define DRV835X_VGS_LA      (1u <<  4)   /* VGS fault low-side A */
#define DRV835X_VGS_HB      (1u <<  3)   /* VGS fault high-side B */
#define DRV835X_VGS_LB      (1u <<  2)   /* VGS fault low-side B */
#define DRV835X_VGS_HC      (1u <<  1)   /* VGS fault high-side C */
#define DRV835X_VGS_LC      (1u <<  0)   /* VGS fault low-side C */

typedef struct {
    uint16_t fault1;   /* raw Fault Status 1 register */
    uint16_t vgs2;     /* raw VGS Status 2 register   */
} DRV835x_Status_t;

void DRV835x_Configure(void);   /* write gain=10 V/V to CSA Control register */
void DRV835x_CalibrateCSA(void); /* measure and store amp offsets, call once at startup with PWM disabled */
void DRV835x_ReadStatus(DRV835x_Status_t *s);
/* hw_fault: 1 if nFAULT GPIO is asserted (active-low), 0 otherwise */
void DRV835x_PrintFaults(const DRV835x_Status_t *s, int hw_fault);

/* Returns 1 if any fault bit is set */
static inline int DRV835x_HasFault(const DRV835x_Status_t *s)
{
    return (s->fault1 & DRV835X_FAULT) ? 1 : 0;
}

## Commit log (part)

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2026-05-27 Almost done rev 1.1
2026-06-04 Revision 1.1
2026-06-04 Added readme
2026-06-04 Added images of board
2026-06-04 Add hardware section to README with images
    Added hardware section with images of the motor controller.
2026-06-04 Update Power MOSFETs specification in README
    Removed the quantity of Power MOSFETs listed in the specifications.
2026-06-04 Restructure repo, add .gitignore, remove build artifacts
2026-06-04 Removed redundant files
2026-06-12 Rev 1.2
